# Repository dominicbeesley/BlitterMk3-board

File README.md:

# BlitterMk3-board
A 6502 FPGA development board targeted at the BBC Micro/Electron range of computers but hopefully also suitable for any 6502/65c02 or 65816 based computer

## Features

- Intel MAX 10 FPGA (10MXXDCF256) in size ranging from 4000 to 50000 LEs
- HDMI output from FPGA via LVDS pins (experimental)
- stereo 1 bit DAC
- uSD card
- Battery backup with optional supervisor IC and memory lockout
- i2c Real time clock
- i2c Flash EEPROM
- parallel 8-bit 55ns flash ROM 39x040 (512kB)
- up to 4 TSOP-II 44 RAM chips for up to 8MB RAM, 1 chip can be optionally battery backed
- 6502/65C02/6512/65102/65112/65816 compatible plug (configurable with jumpers/firmware)
- 5V compatible expansion headers for hosting hard CPU or Raspberry PI Zero

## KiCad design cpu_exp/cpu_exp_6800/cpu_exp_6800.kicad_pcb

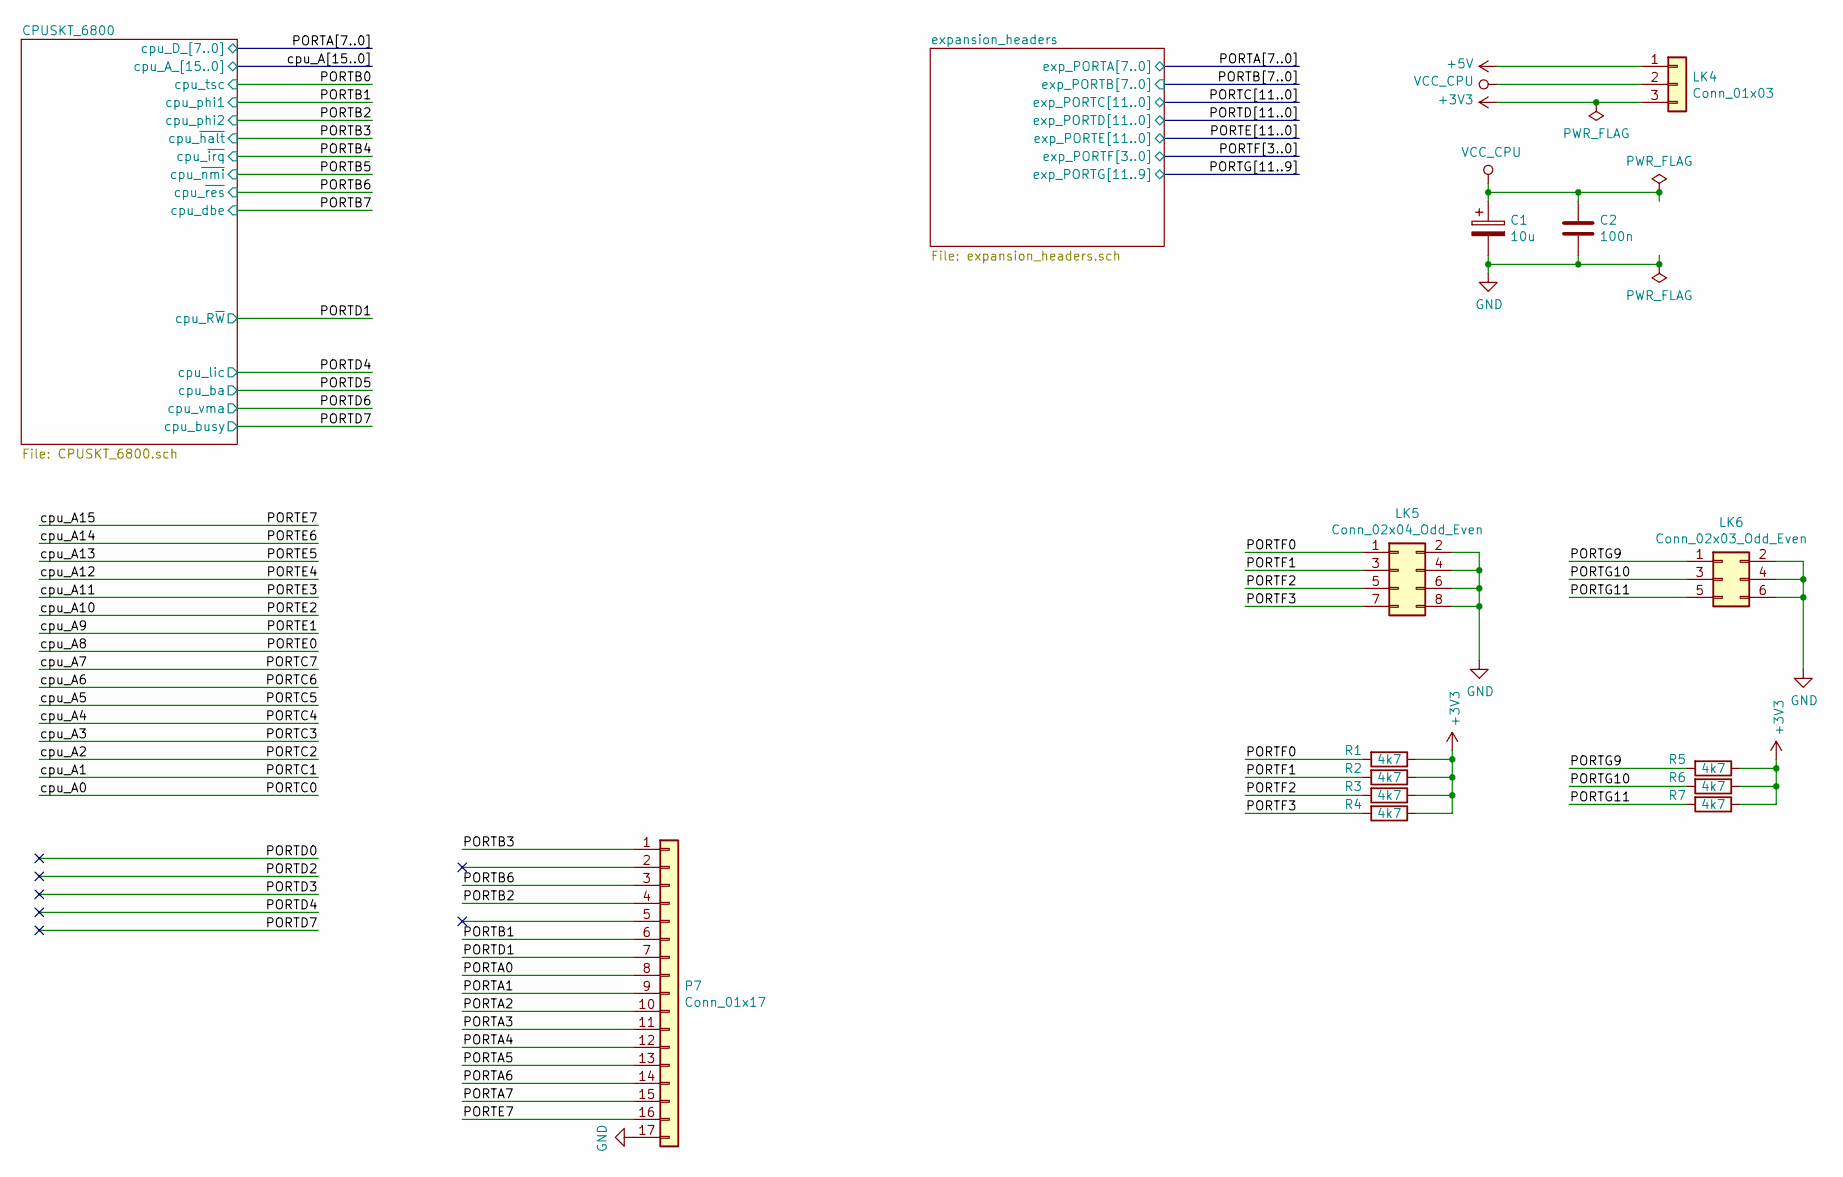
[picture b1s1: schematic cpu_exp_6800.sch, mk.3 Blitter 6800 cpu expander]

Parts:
C1: 10u; C_1206
C2: 100n; C_1206
LK4: Conn_01x03; PinHeader_1x03_P2.54mm_Vertical
LK5: Conn_02x04_Odd_Even; PinHeader_2x04_P2.54mm_Vertical
LK6: Conn_02x03_Odd_Even; PinHeader_2x03_P2.54mm_Vertical
P7: Conn_01x17; PinHeader_1x17_P2.54mm_Vertical
R1, R2, R3, R4, R5, R6, R7: 4k7; R_1206

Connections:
+3V3: LK4.3, R1.1, R2.1, R3.1, R4.1, R5.1, R6.1, R7.1; also elsewhere on the board
+5V: LK4.1; also elsewhere on the board
/PORTA0: P7.8; also elsewhere on the board
/PORTA1: P7.9; also elsewhere on the board
/PORTA2: P7.10; also elsewhere on the board
/PORTA3: P7.11; also elsewhere on the board
/PORTA4: P7.12; also elsewhere on the board
/PORTA5: P7.13; also elsewhere on the board
/PORTA6: P7.14; also elsewhere on the board
/PORTA7: P7.15; also elsewhere on the board
/PORTB1: P7.6; also elsewhere on the board
/PORTB2: P7.4; also elsewhere on the board
/PORTB3: P7.1; also elsewhere on the board
/PORTB6: P7.3; also elsewhere on the board
/PORTD1: P7.7; also elsewhere on the board
/PORTE7: P7.16; also elsewhere on the board
/PORTF0: LK5.1, R1.2; also elsewhere on the board
/PORTF1: LK5.3, R2.2; also elsewhere on the board
/PORTF2: LK5.5, R3.2; also elsewhere on the board
/PORTF3: LK5.7, R4.2; also elsewhere on the board
/PORTG9: LK6.1, R5.2; also elsewhere on the board
/PORTG10: LK6.3, R6.2; also elsewhere on the board
/PORTG11: LK6.5, R7.2; also elsewhere on the board
GND: C1.2, C2.2, LK5.2, LK5.4, LK5.6, LK5.8, LK6.2, LK6.4, LK6.6, P7.17; also elsewhere on the board
VCC_CPU: C1.1, C2.1, LK4.2; also elsewhere on the board

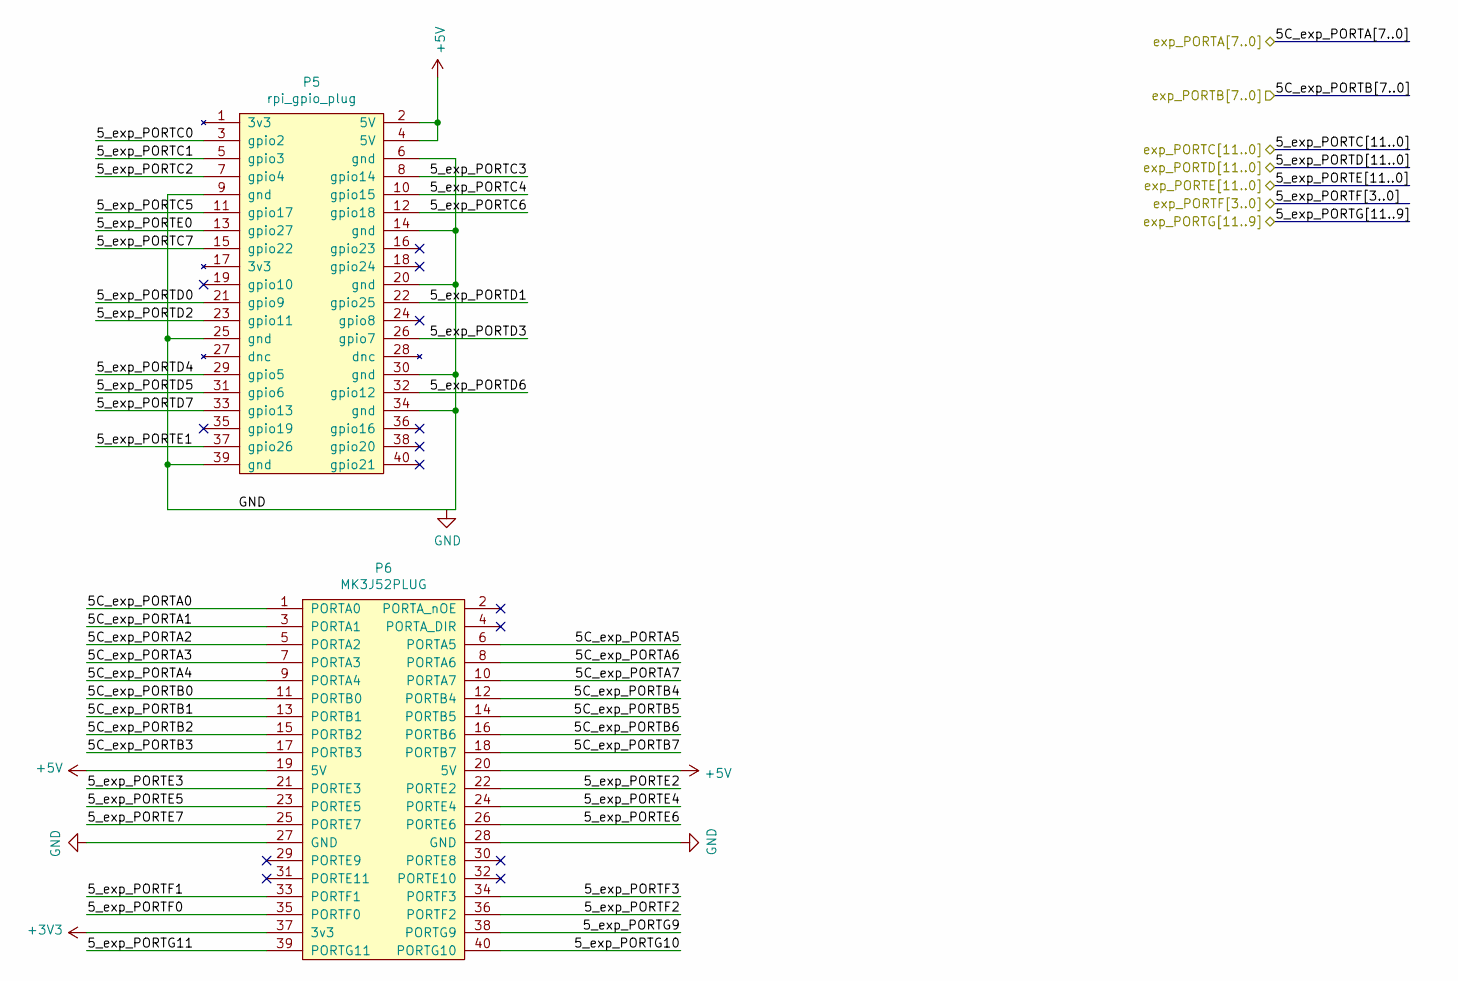
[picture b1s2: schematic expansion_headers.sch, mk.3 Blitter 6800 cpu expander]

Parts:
P5: rpi_gpio_plug; PinHeader_2x20_P2.54mm_Vertical_SMD-dom
P6: MK3J52PLUG; PinSocket_2x20_P2.54mm_Vertical_SMD-dom

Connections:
+3V3: P6.37 (3v3); also elsewhere on the board
+5V: P5.2 (5V), P5.4 (5V), P6.19 (5V), P6.20 (5V); also elsewhere on the board
/PORTA0: P6.1 (PORTA0); also elsewhere on the board
/PORTA1: P6.3 (PORTA1); also elsewhere on the board
/PORTA2: P6.5 (PORTA2); also elsewhere on the board
/PORTA3: P6.7 (PORTA3); also elsewhere on the board
/PORTA4: P6.9 (PORTA4); also elsewhere on the board
/PORTA5: P6.6 (PORTA5); also elsewhere on the board
/PORTA6: P6.8 (PORTA6); also elsewhere on the board
/PORTA7: P6.10 (PORTA7); also elsewhere on the board
/PORTB0: P6.11 (PORTB0); also elsewhere on the board
/PORTB1: P6.13 (PORTB1); also elsewhere on the board
/PORTB2: P6.15 (PORTB2); also elsewhere on the board
/PORTB3: P6.17 (PORTB3); also elsewhere on the board
/PORTB4: P6.12 (PORTB4); also elsewhere on the board
/PORTB5: P6.14 (PORTB5); also elsewhere on the board
/PORTB6: P6.16 (PORTB6); also elsewhere on the board
/PORTB7: P6.18 (PORTB7); also elsewhere on the board
/PORTC0: P5.3 (gpio2); also elsewhere on the board
/PORTC1: P5.5 (gpio3); also elsewhere on the board
/PORTC2: P5.7 (gpio4); also elsewhere on the board
/PORTC3: P5.8 (gpio14); also elsewhere on the board
/PORTC4: P5.10 (gpio15); also elsewhere on the board
/PORTC5: P5.11 (gpio17); also elsewhere on the board
/PORTC6: P5.12 (gpio18); also elsewhere on the board
/PORTC7: P5.15 (gpio22); also elsewhere on the board
/PORTD0: P5.21 (gpio9)
/PORTD1: P5.22 (gpio25); also elsewhere on the board
/PORTD2: P5.23 (gpio11)
/PORTD3: P5.26 (gpio7)
/PORTD4: P5.29 (gpio5)
/PORTD5: P5.31 (gpio6); also elsewhere on the board
/PORTD6: P5.32 (gpio12); also elsewhere on the board
/PORTD7: P5.33 (gpio13)
/PORTE0: P5.13 (gpio27); also elsewhere on the board
/PORTE1: P5.37 (gpio26); also elsewhere on the board
/PORTE2: P6.22 (PORTE2); also elsewhere on the board
/PORTE3: P6.21 (PORTE3); also elsewhere on the board
/PORTE4: P6.24 (PORTE4); also elsewhere on the board
/PORTE5: P6.23 (PORTE5); also elsewhere on the board
/PORTE6: P6.26 (PORTE6); also elsewhere on the board
/PORTE7: P6.25 (PORTE7); also elsewhere on the board
/PORTF0: P6.35 (PORTF0); also elsewhere on the board
/PORTF1: P6.33 (PORTF1); also elsewhere on the board
/PORTF2: P6.36 (PORTF2); also elsewhere on the board
/PORTF3: P6.34 (PORTF3); also elsewhere on the board
/PORTG9: P6.38 (PORTG9); also elsewhere on the board
/PORTG10: P6.40 (PORTG10); also elsewhere on the board
/PORTG11: P6.39 (PORTG11); also elsewhere on the board
GND: P5.6 (gnd), P5.9 (gnd), P5.14 (gnd), P5.20 (gnd), P5.25 (gnd), P5.30 (gnd), P5.34 (gnd), P5.39 (gnd), P6.27 (GND), P6.28 (GND); also elsewhere on the board

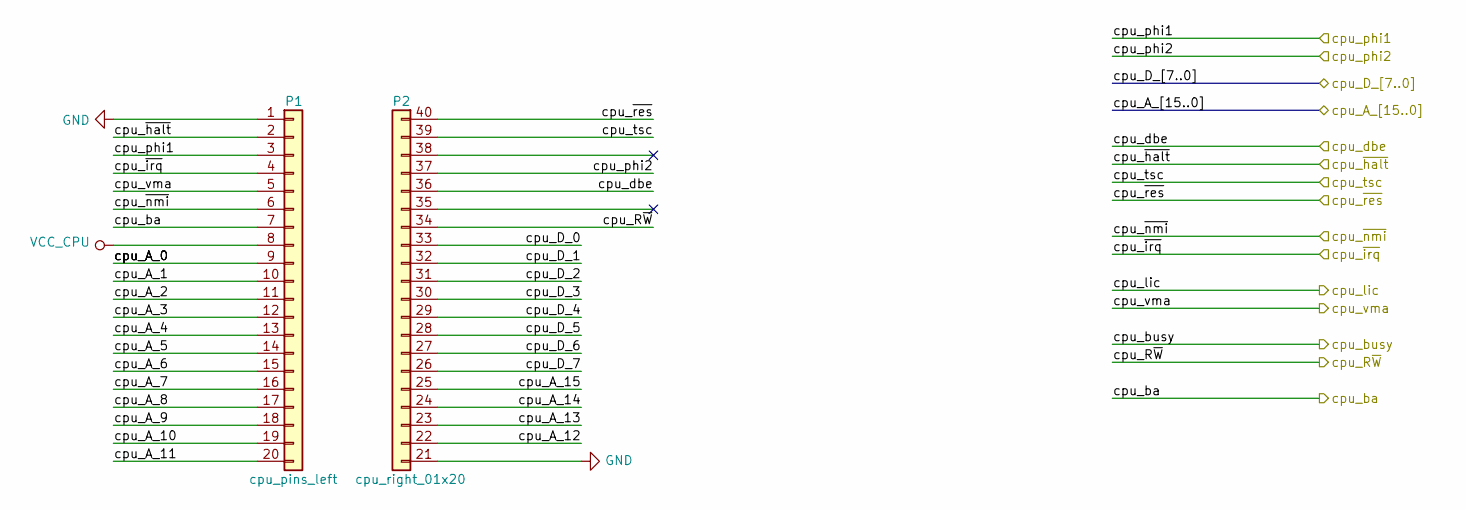
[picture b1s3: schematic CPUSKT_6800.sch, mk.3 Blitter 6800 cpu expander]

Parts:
P1: cpu_pins_left; PinSocket_1x20_P2.54mm_Vertical
P2: cpu_right_01x20; Pin_Header_Straight_1x20_Pitch2.54mm_21_40

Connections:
/PORTA0: P2.33; also elsewhere on the board
/PORTA1: P2.32; also elsewhere on the board
/PORTA2: P2.31; also elsewhere on the board
/PORTA3: P2.30; also elsewhere on the board
/PORTA4: P2.29; also elsewhere on the board
/PORTA5: P2.28; also elsewhere on the board
/PORTA6: P2.27; also elsewhere on the board
/PORTA7: P2.26; also elsewhere on the board
/PORTB0: P2.39; also elsewhere on the board
/PORTB1: P1.3; also elsewhere on the board
/PORTB2: P2.37; also elsewhere on the board
/PORTB3: P1.2; also elsewhere on the board
/PORTB4: P1.4; also elsewhere on the board
/PORTB5: P1.6; also elsewhere on the board
/PORTB6: P2.40; also elsewhere on the board
/PORTB7: P2.36; also elsewhere on the board
/PORTC0: P1.9; also elsewhere on the board
/PORTC1: P1.10; also elsewhere on the board
/PORTC2: P1.11; also elsewhere on the board
/PORTC3: P1.12; also elsewhere on the board
/PORTC4: P1.13; also elsewhere on the board
/PORTC5: P1.14; also elsewhere on the board
/PORTC6: P1.15; also elsewhere on the board
/PORTC7: P1.16; also elsewhere on the board
/PORTD1: P2.34; also elsewhere on the board
/PORTD5: P1.7; also elsewhere on the board
/PORTD6: P1.5; also elsewhere on the board
/PORTE0: P1.17; also elsewhere on the board
/PORTE1: P1.18; also elsewhere on the board
/PORTE2: P1.19; also elsewhere on the board
/PORTE3: P1.20; also elsewhere on the board
/PORTE4: P2.22; also elsewhere on the board
/PORTE5: P2.23; also elsewhere on the board
/PORTE6: P2.24; also elsewhere on the board
/PORTE7: P2.25; also elsewhere on the board
GND: P1.1, P2.21; also elsewhere on the board
VCC_CPU: P1.8; also elsewhere on the board

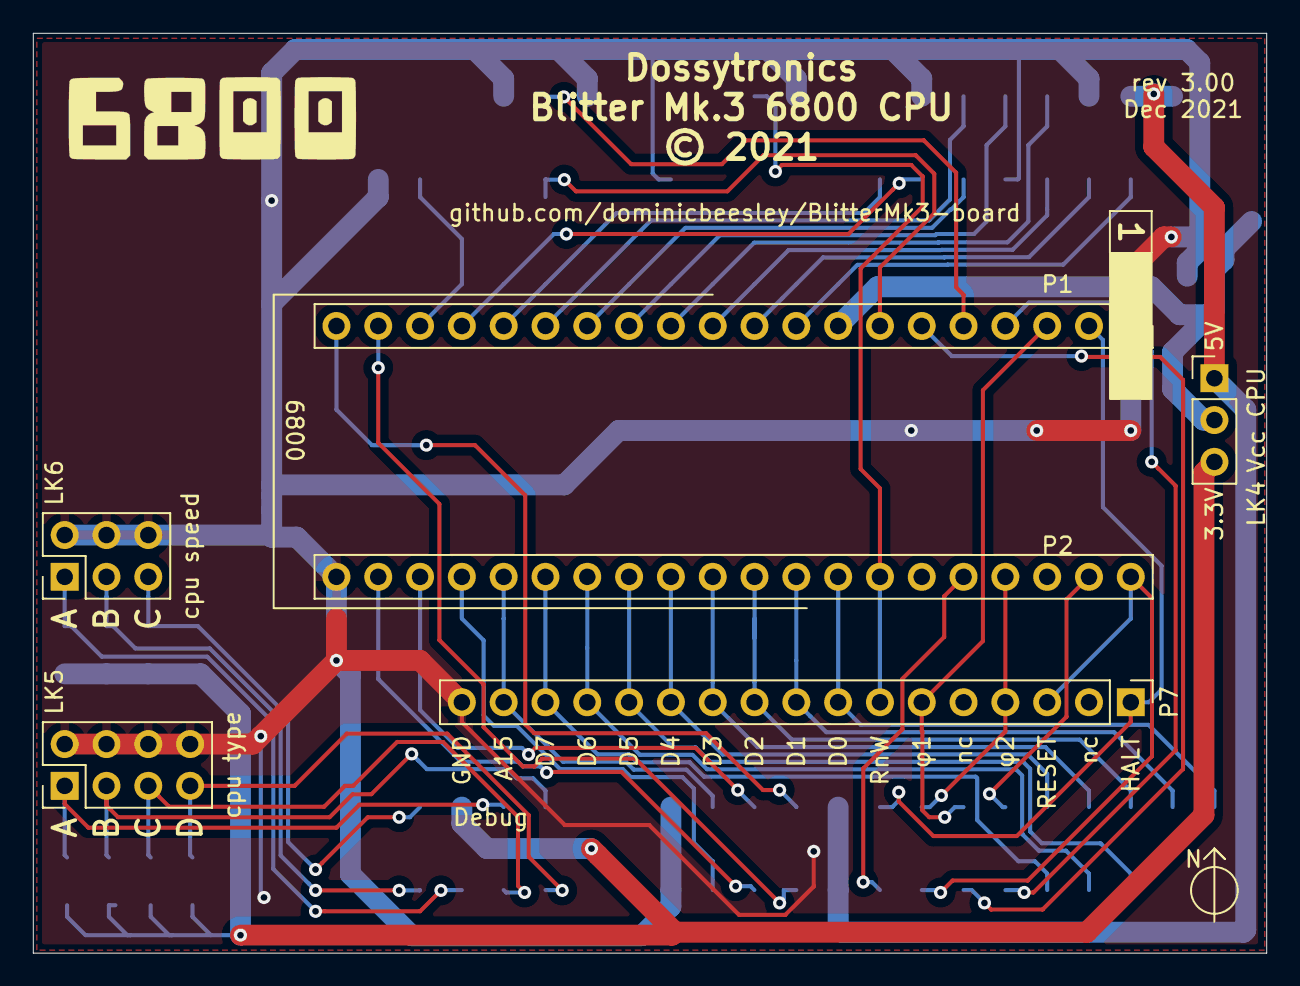
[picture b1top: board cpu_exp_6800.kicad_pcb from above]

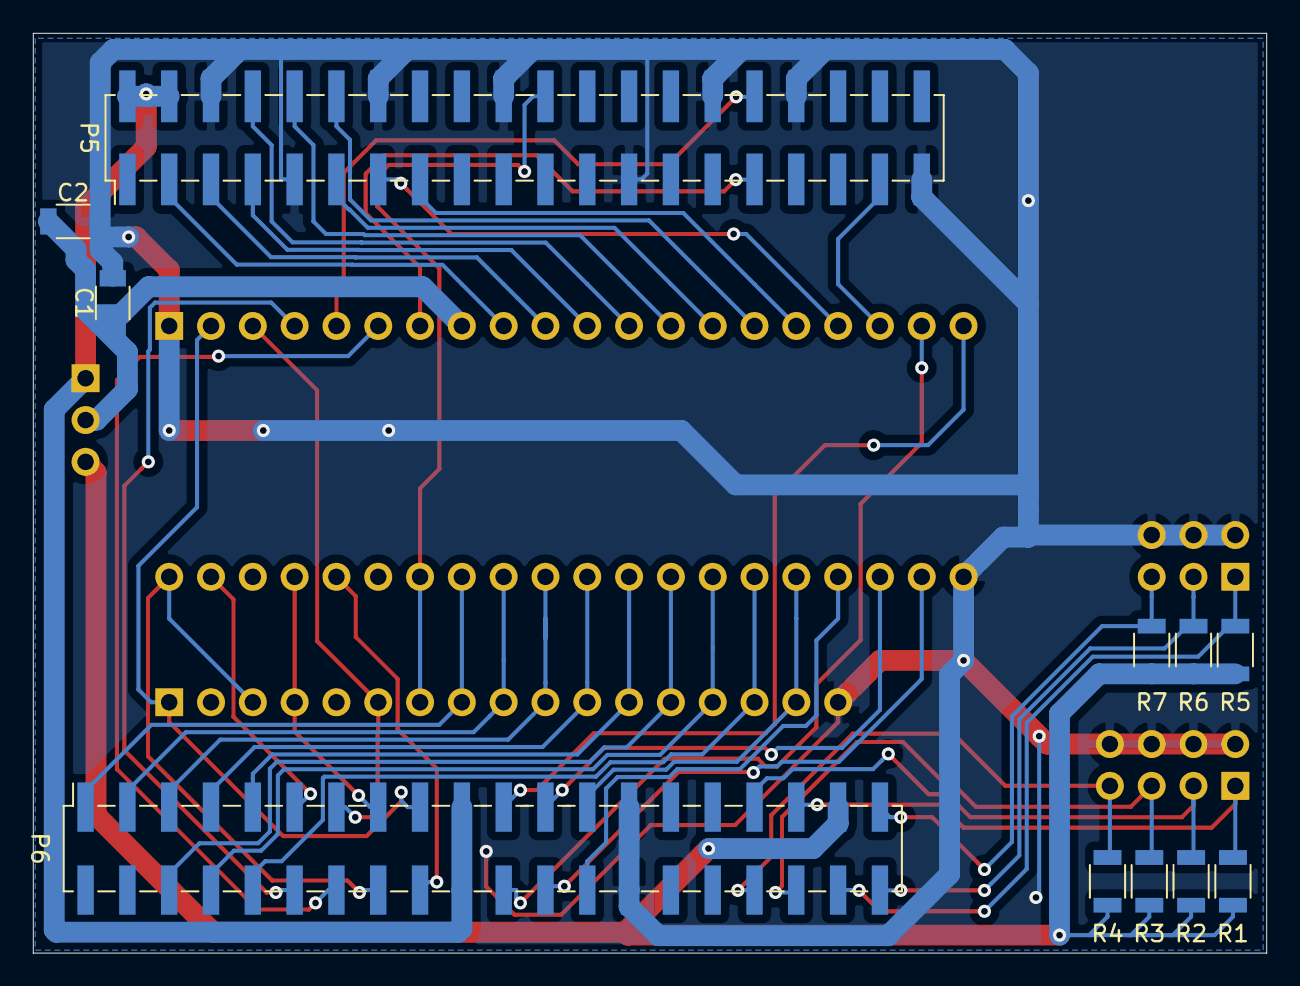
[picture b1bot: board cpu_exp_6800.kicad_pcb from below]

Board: 2 copper layers, 74.9 x 55.9 mm, 17 parts (11 on the bottom side), 46 nets.

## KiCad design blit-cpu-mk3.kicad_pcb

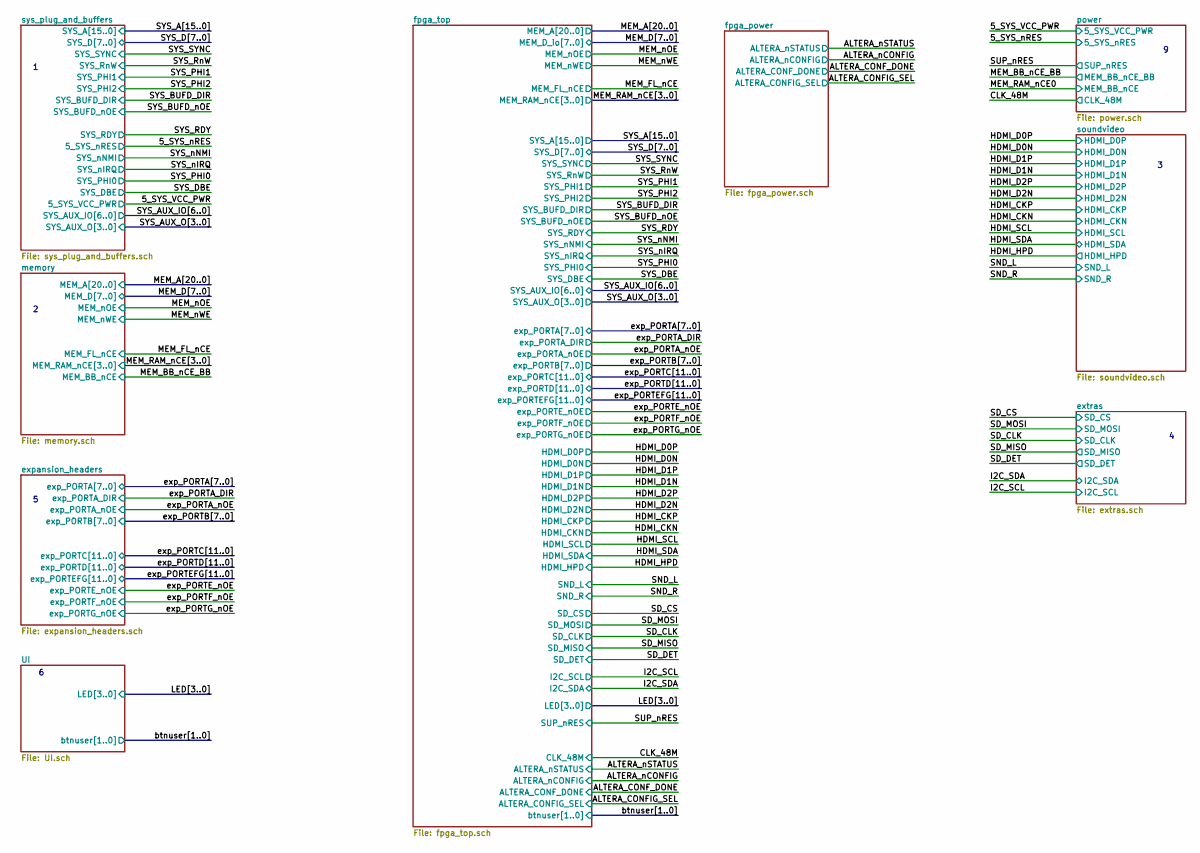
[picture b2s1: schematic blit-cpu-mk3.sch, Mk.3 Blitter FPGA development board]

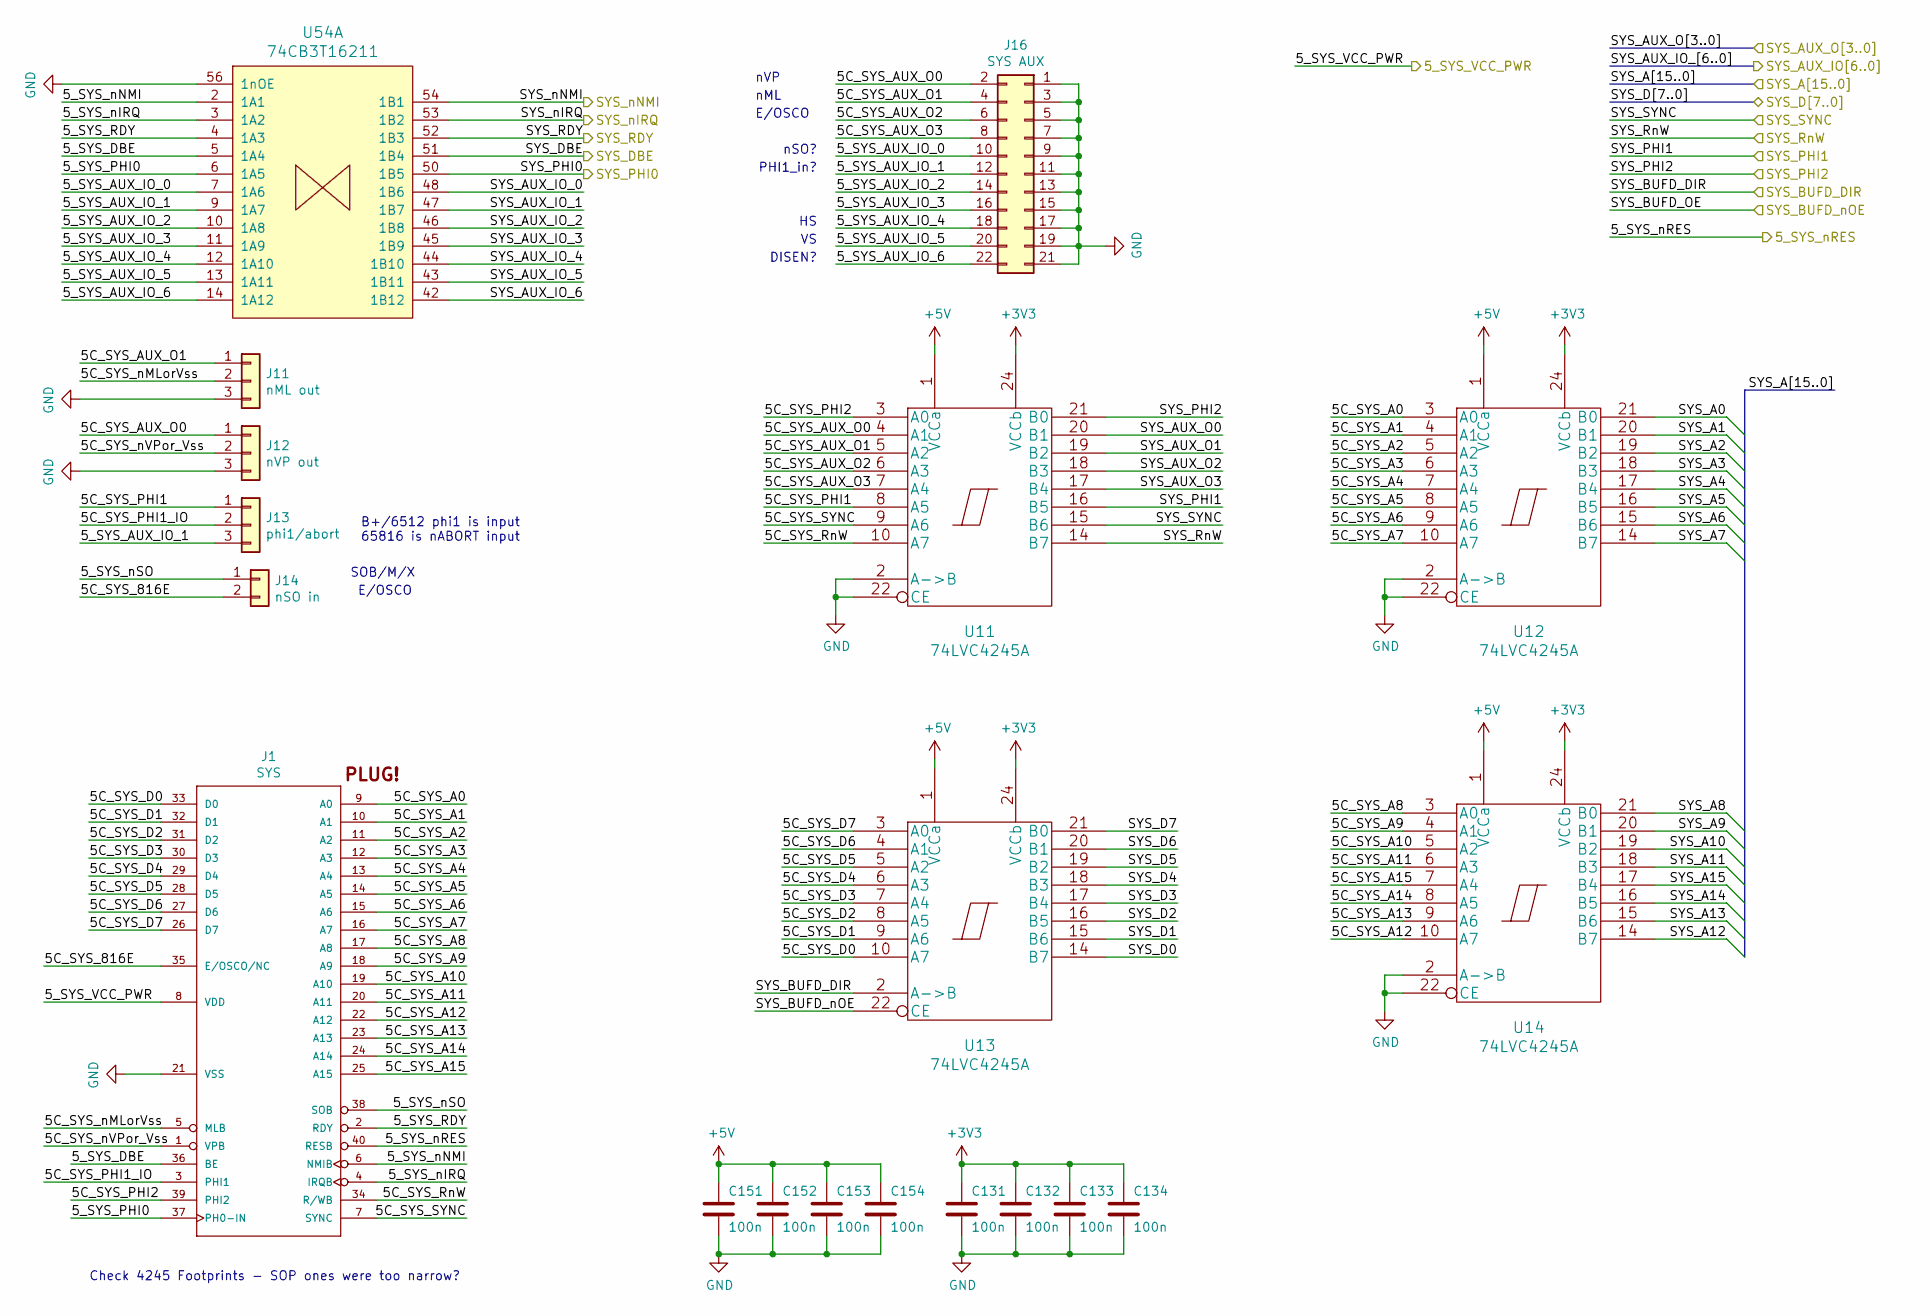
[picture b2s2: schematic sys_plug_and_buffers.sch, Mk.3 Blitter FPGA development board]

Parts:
C131, C132, C133, C134, C151, C152, C153, C154: 100n; C_0805
J1: SYS; DIP-40_W16.51mm_SMDSocket_LongPads-flipped
J11: nML out; PinHeader_1x03_P2.54mm_Vertical
J12: nVP out; PinHeader_1x03_P2.54mm_Vertical
J13: phi1/abort; PinHeader_1x03_P2.54mm_Vertical
J14: nSO in; PinHeader_1x02_P2.54mm_Vertical
J16: SYS AUX; PinHeader_2x11_P2.54mm_Vertical
U11, U12, U13, U14: 74LVC4245A; TSSOP-24_4.4x7.8mm_Pitch0.65mm
U54: 74CB3T16211; TSSOP-56_6.1x14mm_Pitch0.5mm

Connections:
+3V3: C131.1, C132.1, C133.1, C134.1, U11.23 (VCCb), U11.24 (VCCb), U12.23 (VCCb), U12.24 (VCCb), U13.23 (VCCb), U13.24 (VCCb), U14.23 (VCCb), U14.24 (VCCb); also elsewhere on the board
+5V: C151.1, C152.1, C153.1, C154.1, U11.1 (VCCa), U12.1 (VCCa), U13.1 (VCCa), U14.1 (VCCa); also elsewhere on the board
/5_SYS_VCC_PWR: J1.8 (VDD); also elsewhere on the board
/5_SYS_nRES: J1.40 (RESB); also elsewhere on the board
/SYS_BUFD_DIR: U13.2 (A->B); also elsewhere on the board
/SYS_BUFD_nOE: U13.22 (CE); also elsewhere on the board
/SYS_DBE: U54.51 (1B4); also elsewhere on the board
/SYS_PHI0: U54.50 (1B5); also elsewhere on the board
/SYS_PHI1: U11.16 (B5); also elsewhere on the board
/SYS_PHI2: U11.21 (B0); also elsewhere on the board
/SYS_RDY: U54.52 (1B3); also elsewhere on the board
/SYS_RnW: U11.14 (B7); also elsewhere on the board
/SYS_SYNC: U11.15 (B6); also elsewhere on the board
/SYS_nIRQ: U54.53 (1B2); also elsewhere on the board
/SYS_nNMI: U54.54 (1B1); also elsewhere on the board
/sys_plug_and_buffers/5C_SYS_816E: J1.35 (E/OSCO/NC), J14.2
/sys_plug_and_buffers/5C_SYS_A0: J1.9 (A0), U12.3 (A0)
/sys_plug_and_buffers/5C_SYS_A1: J1.10 (A1), U12.4 (A1)
/sys_plug_and_buffers/5C_SYS_A2: J1.11 (A2), U12.5 (A2)
/sys_plug_and_buffers/5C_SYS_A3: J1.12 (A3), U12.6 (A3)
/sys_plug_and_buffers/5C_SYS_A4: J1.13 (A4), U12.7 (A4)
/sys_plug_and_buffers/5C_SYS_A5: J1.14 (A5), U12.8 (A5)
/sys_plug_and_buffers/5C_SYS_A6: J1.15 (A6), U12.9 (A6)
/sys_plug_and_buffers/5C_SYS_A7: J1.16 (A7), U12.10 (A7)
/sys_plug_and_buffers/5C_SYS_A8: J1.17 (A8), U14.3 (A0)
/sys_plug_and_buffers/5C_SYS_A9: J1.18 (A9), U14.4 (A1)
/sys_plug_and_buffers/5C_SYS_A10: J1.19 (A10), U14.5 (A2)
/sys_plug_and_buffers/5C_SYS_A11: J1.20 (A11), U14.6 (A3)
/sys_plug_and_buffers/5C_SYS_A12: J1.22 (A12), U14.10 (A7)
/sys_plug_and_buffers/5C_SYS_A13: J1.23 (A13), U14.9 (A6)
/sys_plug_and_buffers/5C_SYS_A14: J1.24 (A14), U14.8 (A5)
/sys_plug_and_buffers/5C_SYS_A15: J1.25 (A15), U14.7 (A4)
/sys_plug_and_buffers/5C_SYS_AUX_O0: J12.1, J16.2, U11.4 (A1)
/sys_plug_and_buffers/5C_SYS_AUX_O1: J11.1, J16.4, U11.5 (A2)
/sys_plug_and_buffers/5C_SYS_AUX_O2: J16.6, U11.6 (A3)
/sys_plug_and_buffers/5C_SYS_AUX_O3: J16.8, U11.7 (A4)
/sys_plug_and_buffers/5C_SYS_D0: J1.33 (D0), U13.10 (A7)
/sys_plug_and_buffers/5C_SYS_D1: J1.32 (D1), U13.9 (A6)
/sys_plug_and_buffers/5C_SYS_D2: J1.31 (D2), U13.8 (A5)
/sys_plug_and_buffers/5C_SYS_D3: J1.30 (D3), U13.7 (A4)
/sys_plug_and_buffers/5C_SYS_D4: J1.29 (D4), U13.6 (A3)
/sys_plug_and_buffers/5C_SYS_D5: J1.28 (D5), U13.5 (A2)
/sys_plug_and_buffers/5C_SYS_D6: J1.27 (D6), U13.4 (A1)
/sys_plug_and_buffers/5C_SYS_D7: J1.26 (D7), U13.3 (A0)
/sys_plug_and_buffers/5C_SYS_PHI1: J13.1, U11.8 (A5)
/sys_plug_and_buffers/5C_SYS_PHI1_IO: J1.3 (PHI1), J13.2
/sys_plug_and_buffers/5C_SYS_PHI2: J1.39 (PHI2), U11.3 (A0)
/sys_plug_and_buffers/5C_SYS_RnW: J1.34 (R/WB), U11.10 (A7)
/sys_plug_and_buffers/5C_SYS_SYNC: J1.7 (SYNC), U11.9 (A6)
/sys_plug_and_buffers/5C_SYS_nMLorVss: J1.5 (MLB), J11.2
/sys_plug_and_buffers/5C_SYS_nVPor_Vss: J1.1 (VPB), J12.2
/sys_plug_and_buffers/5_SYS_AUX_IO_0: J16.10, U54.7 (1A6)
/sys_plug_and_buffers/5_SYS_AUX_IO_1: J13.3, J16.12, U54.9 (1A7)
/sys_plug_and_buffers/5_SYS_AUX_IO_2: J16.14, U54.10 (1A8)
/sys_plug_and_buffers/5_SYS_AUX_IO_3: J16.16, U54.11 (1A9)
/sys_plug_and_buffers/5_SYS_AUX_IO_4: J16.18, U54.12 (1A10)
/sys_plug_and_buffers/5_SYS_AUX_IO_5: J16.20, U54.13 (1A11)
/sys_plug_and_buffers/5_SYS_AUX_IO_6: J16.22, U54.14 (1A12)
/sys_plug_and_buffers/5_SYS_DBE: J1.36 (BE), U54.5 (1A4)
/sys_plug_and_buffers/5_SYS_PHI0: J1.37 (PH0-IN), U54.6 (1A5)
/sys_plug_and_buffers/5_SYS_RDY: J1.2 (RDY), U54.4 (1A3)
/sys_plug_and_buffers/5_SYS_nIRQ: J1.4 (IRQB), U54.3 (1A2)
/sys_plug_and_buffers/5_SYS_nNMI: J1.6 (NMIB), U54.2 (1A1)
/sys_plug_and_buffers/5_SYS_nSO: J1.38 (SOB), J14.1
/sys_plug_and_buffers/SYS_A0: U12.21 (B0); also elsewhere on the board
/sys_plug_and_buffers/SYS_A1: U12.20 (B1); also elsewhere on the board
/sys_plug_and_buffers/SYS_A2: U12.19 (B2); also elsewhere on the board
/sys_plug_and_buffers/SYS_A3: U12.18 (B3); also elsewhere on the board
/sys_plug_and_buffers/SYS_A4: U12.17 (B4); also elsewhere on the board
/sys_plug_and_buffers/SYS_A5: U12.16 (B5); also elsewhere on the board
/sys_plug_and_buffers/SYS_A6: U12.15 (B6); also elsewhere on the board
/sys_plug_and_buffers/SYS_A7: U12.14 (B7); also elsewhere on the board
/sys_plug_and_buffers/SYS_A8: U14.21 (B0); also elsewhere on the board
/sys_plug_and_buffers/SYS_A9: U14.20 (B1); also elsewhere on the board
/sys_plug_and_buffers/SYS_A10: U14.19 (B2); also elsewhere on the board
/sys_plug_and_buffers/SYS_A11: U14.18 (B3); also elsewhere on the board
/sys_plug_and_buffers/SYS_A12: U14.14 (B7); also elsewhere on the board
/sys_plug_and_buffers/SYS_A13: U14.15 (B6); also elsewhere on the board
/sys_plug_and_buffers/SYS_A14: U14.16 (B5); also elsewhere on the board
/sys_plug_and_buffers/SYS_A15: U14.17 (B4); also elsewhere on the board
/sys_plug_and_buffers/SYS_AUX_IO_0: U54.48 (1B6); also elsewhere on the board
/sys_plug_and_buffers/SYS_AUX_IO_1: U54.47 (1B7); also elsewhere on the board
/sys_plug_and_buffers/SYS_AUX_IO_2: U54.46 (1B8); also elsewhere on the board
/sys_plug_and_buffers/SYS_AUX_IO_3: U54.45 (1B9); also elsewhere on the board
/sys_plug_and_buffers/SYS_AUX_IO_4: U54.44 (1B10); also elsewhere on the board
/sys_plug_and_buffers/SYS_AUX_IO_5: U54.43 (1B11); also elsewhere on the board
/sys_plug_and_buffers/SYS_AUX_IO_6: U54.42 (1B12); also elsewhere on the board
/sys_plug_and_buffers/SYS_AUX_O0: U11.20 (B1); also elsewhere on the board
/sys_plug_and_buffers/SYS_AUX_O1: U11.19 (B2); also elsewhere on the board
/sys_plug_and_buffers/SYS_AUX_O2: U11.18 (B3); also elsewhere on the board
/sys_plug_and_buffers/SYS_AUX_O3: U11.17 (B4); also elsewhere on the board
/sys_plug_and_buffers/SYS_D0: U13.14 (B7); also elsewhere on the board
/sys_plug_and_buffers/SYS_D1: U13.15 (B6); also elsewhere on the board
/sys_plug_and_buffers/SYS_D2: U13.16 (B5); also elsewhere on the board
/sys_plug_and_buffers/SYS_D3: U13.17 (B4); also elsewhere on the board
/sys_plug_and_buffers/SYS_D4: U13.18 (B3); also elsewhere on the board
/sys_plug_and_buffers/SYS_D5: U13.19 (B2); also elsewhere on the board
/sys_plug_and_buffers/SYS_D6: U13.20 (B1); also elsewhere on the board
/sys_plug_and_buffers/SYS_D7: U13.21 (B0); also elsewhere on the board

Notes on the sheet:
B+/6512 phi1 is input 65816 is nABORT input
DISEN?
PHI1_in?
SOB/M/X
nSO?
nML
nVP
E/OSCO
Check 4245 Footprints - SOP ones were too narrow?

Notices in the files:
testpinsquartus/mk3pinstest.qsf:
Copyright (C) 2018  Intel Corporation. All rights reserved.
cpu_exp/cpu_exp_65xx_6x09/cpu_exp_65xx_6x09.kicad_pcb:
© 2019
cpu_exp/cpu_exp_6800/cpu_exp_6800.kicad_pcb:
© 2021
